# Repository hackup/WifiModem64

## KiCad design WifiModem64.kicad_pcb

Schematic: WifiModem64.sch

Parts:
C1: 100n; C_0805_HandSoldering
D1: B5819WS; D_SOD-323_HandSoldering
F1: 0.5A; R_1206_HandSoldering
J1: C64-UserPort; C64-User-Port-Female
J2: USB_B; USB_Micro-B
JP1: PwrSafety; GS2
JP2: CTS; GS2
JP3: RTS; GS2
JP4: SP1; GS2
JP5: SP2; GS2
JP6: PwrSrc; Pin_Header_Straight_1x03_Pitch2.54mm
LED1: WS2812B
Q1, Q2, Q3, Q4: BSS138; SOT-23_Handsoldering
R1, R2, R3, R4, R5, R6, R7, R8: 10k; R_0805_HandSoldering
SW1: Push; SW_Tactile_SPST_Angled_PTS645Vx58-2LFS
SW2: Reset; SW_Tactile_SPST_Angled_PTS645Vx58-2LFS
U1: WeMos_mini; D1_mini_board
U2: WeMos_D1_mini_OLED_Shield; D1_mini_OLED_Display

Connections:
+3V3: Q1.1, Q2.1, Q3.1, Q4.1, R1.1, R2.1, R3.1, R4.1, U1.16, U2.16 (3.3V)
+5V: C1.1, F1.1, JP1.1, LED1.1, R5.1, R6.1, R7.1, R8.1, U1.1, U2.1 (5V)
CTS: J1.D, JP2.1, Q1.2, R1.2
GND: C1.2, J1.1, J1.12, J1.A, J1.N, J2.4, J2.5, LED1.3, SW1.2, SW2.2, U1.2, U2.2 (GND)
unnamed: D1.1, F1.2
unnamed: D1.2, JP1.2, JP6.2
unnamed: J1.2, JP6.3
unnamed: J1.6, J1.L
unnamed: J2.1, JP6.1
RST: J1.3, SW2.1
RTS: J1.K, JP3.1, Q2.2, R2.2
SP1: J1.5, J1.M, JP4.1, Q3.2, R3.2
SP2: J1.7, J1.B, J1.C, JP5.1, Q4.2, R4.2
W_A0: U1.10, U2.10 (A0)
W_D0: U1.11, U2.11 (D0)
W_D1: U1.6, U2.6 (D1)
W_D2: U1.5, U2.5 (D2)
W_D3: SW1.1, U1.4, U2.4 (D3)
W_D4: U1.3, U2.3 (D4)
W_D5: LED1.4, U1.12, U2.12 (D5)
W_D6: JP2.2, Q1.3, R5.2, U1.13, U2.13 (D6)
W_D7: JP3.2, Q2.3, R6.2, U1.14, U2.14 (D7)
W_D8: U1.15, U2.15 (D8)
W_RST: U1.9, U2.9 (Rst)
W_RX: JP4.2, Q3.3, R7.2, U1.7, U2.7 (Rx)
W_TX: JP5.2, Q4.3, R8.2, U1.8, U2.8 (Tx)

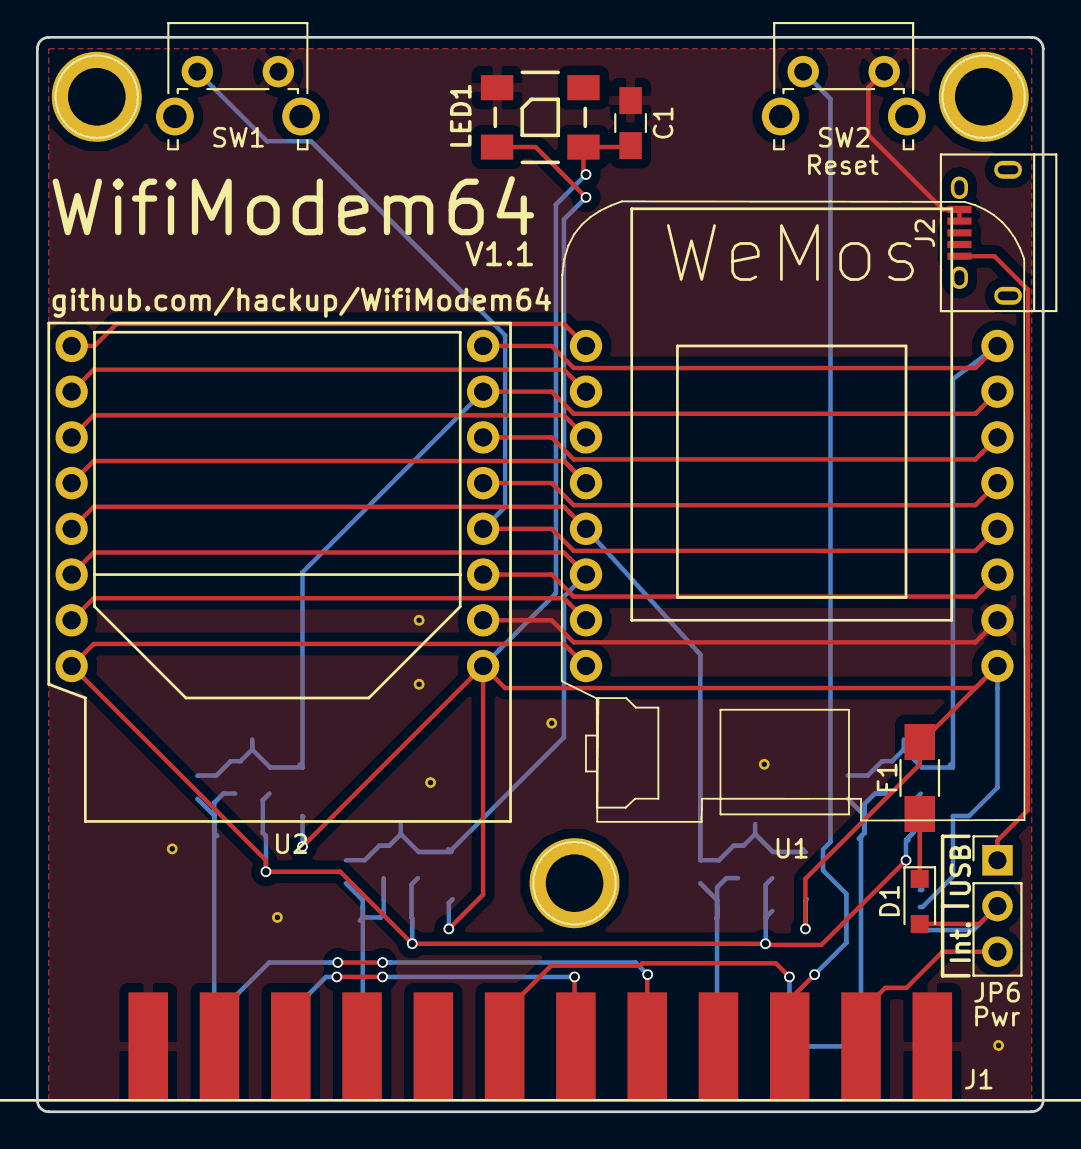
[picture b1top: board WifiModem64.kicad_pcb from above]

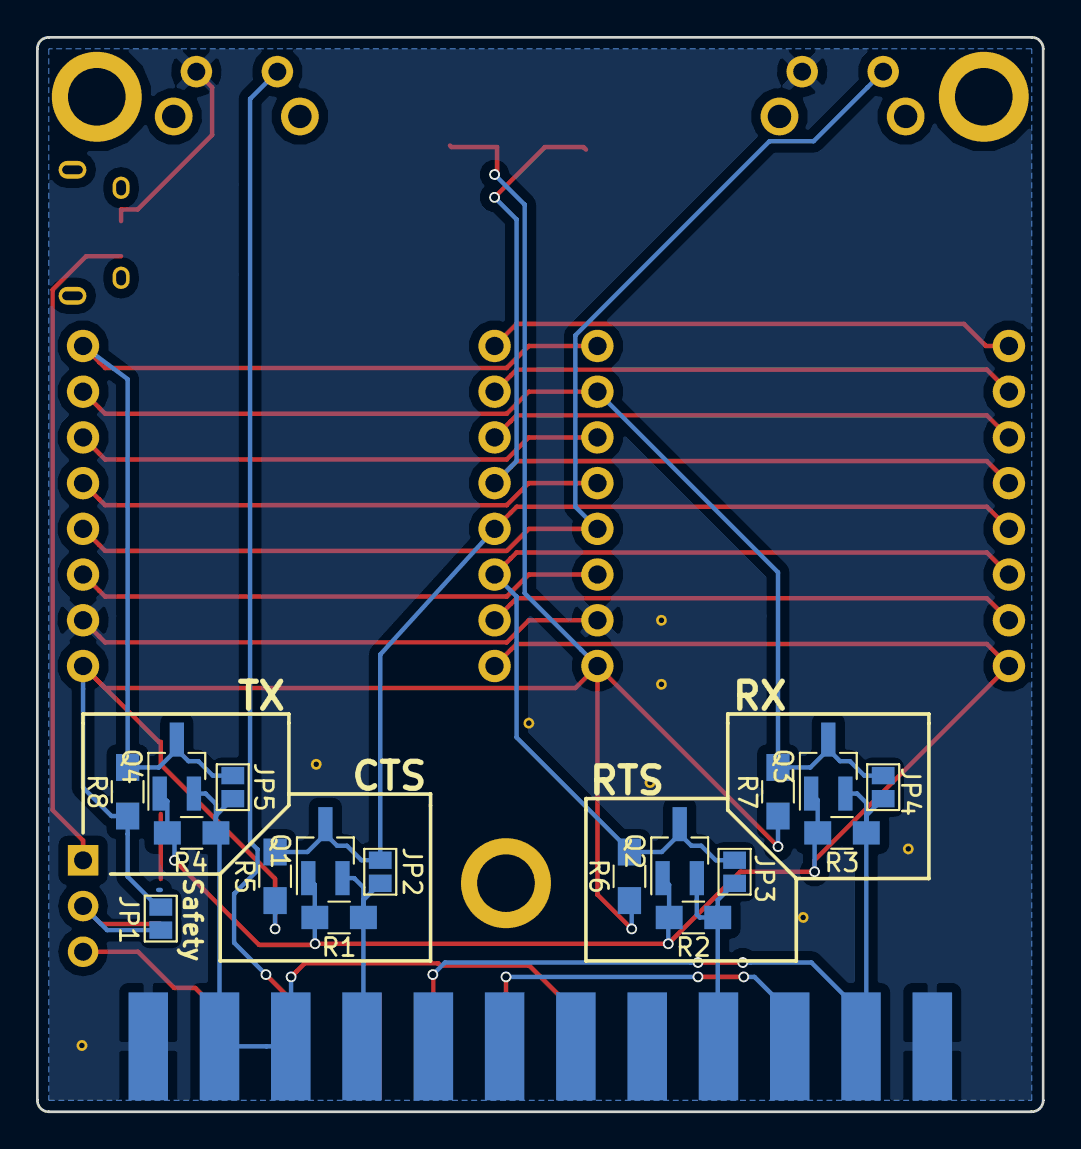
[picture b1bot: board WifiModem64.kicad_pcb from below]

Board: 2 copper layers, 55.9 x 59.7 mm, 28 parts (17 on the bottom side), 26 nets.

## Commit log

2017-12-16 Initial commit.
2017-12-16 First attempt to integrate OLED display.
2017-12-17 WiP.
2017-12-17 Optimized silk screen.
2017-12-18 Added LED and mounting holes.
2017-12-18 Added optional USB power supply.
2017-12-18 First Gerber plot.
2017-12-18 Added Y dimension.
2017-12-18 Fix.
2017-12-18 Added pull-down resistor on GPIO15 that is needed for internal flash boot.
2017-12-18 Pull down resistor is not optional so it should be through hole.
2017-12-19 Keep gerber dir.
2017-12-25 Upgraded project files, modfied resistor footprint.
2017-12-25 Those shouldn't have been committed.
2017-12-26 Freed GPIO15 and fixed footprints.
2017-12-26 WS2812b not working on D0.
2018-01-10 Incomplete work on NeoPixel integration.
2018-01-11 Quick-n-dirty build.
2018-01-15 Revision bump.
2018-01-16 Version 1.1 gerber export.
2018-04-25 Trying to appease the WDT.
